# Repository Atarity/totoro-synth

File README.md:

# Totoro synth
Totoro is a portable, analog synth made on top of MCP6004 opamp. It features 2 VCOs (one could act as LFO) and simple VCF. Here it is [a short video demo](https://www.youtube.com/watch?v=yHeWAp9w_LM).

This open-source project based on [original design](https://syntherjack.net/totoro-1-ic-simple-synth/) of SyntherJack's Totoro and published with his permission.

In v1.0.1:
- Some of the components were rearranged
- Batteries moved on top side of PCB so overall assembly is almost 2 times thinner now
- Minor layout issues were fixed.

### Useful links
- [Bill of Materials v1.0.1](https://docs.google.com/spreadsheets/d/1fobkR_ruTiGQf1n50Jt4_U9o5RTrw8VCa_eaik46wdc/edit?usp=sharing)
- [Assembly details (RU)](https://snnkv.com/projects/totoro-slim/)
- [My list of open-source, standalone synths](https://diy-synths.snnkv.com/)

Enjoy the drone (under [CC-BY-NC-SA](https://creativecommons.org/licenses/by-nc-sa/4.0/deed.en))!

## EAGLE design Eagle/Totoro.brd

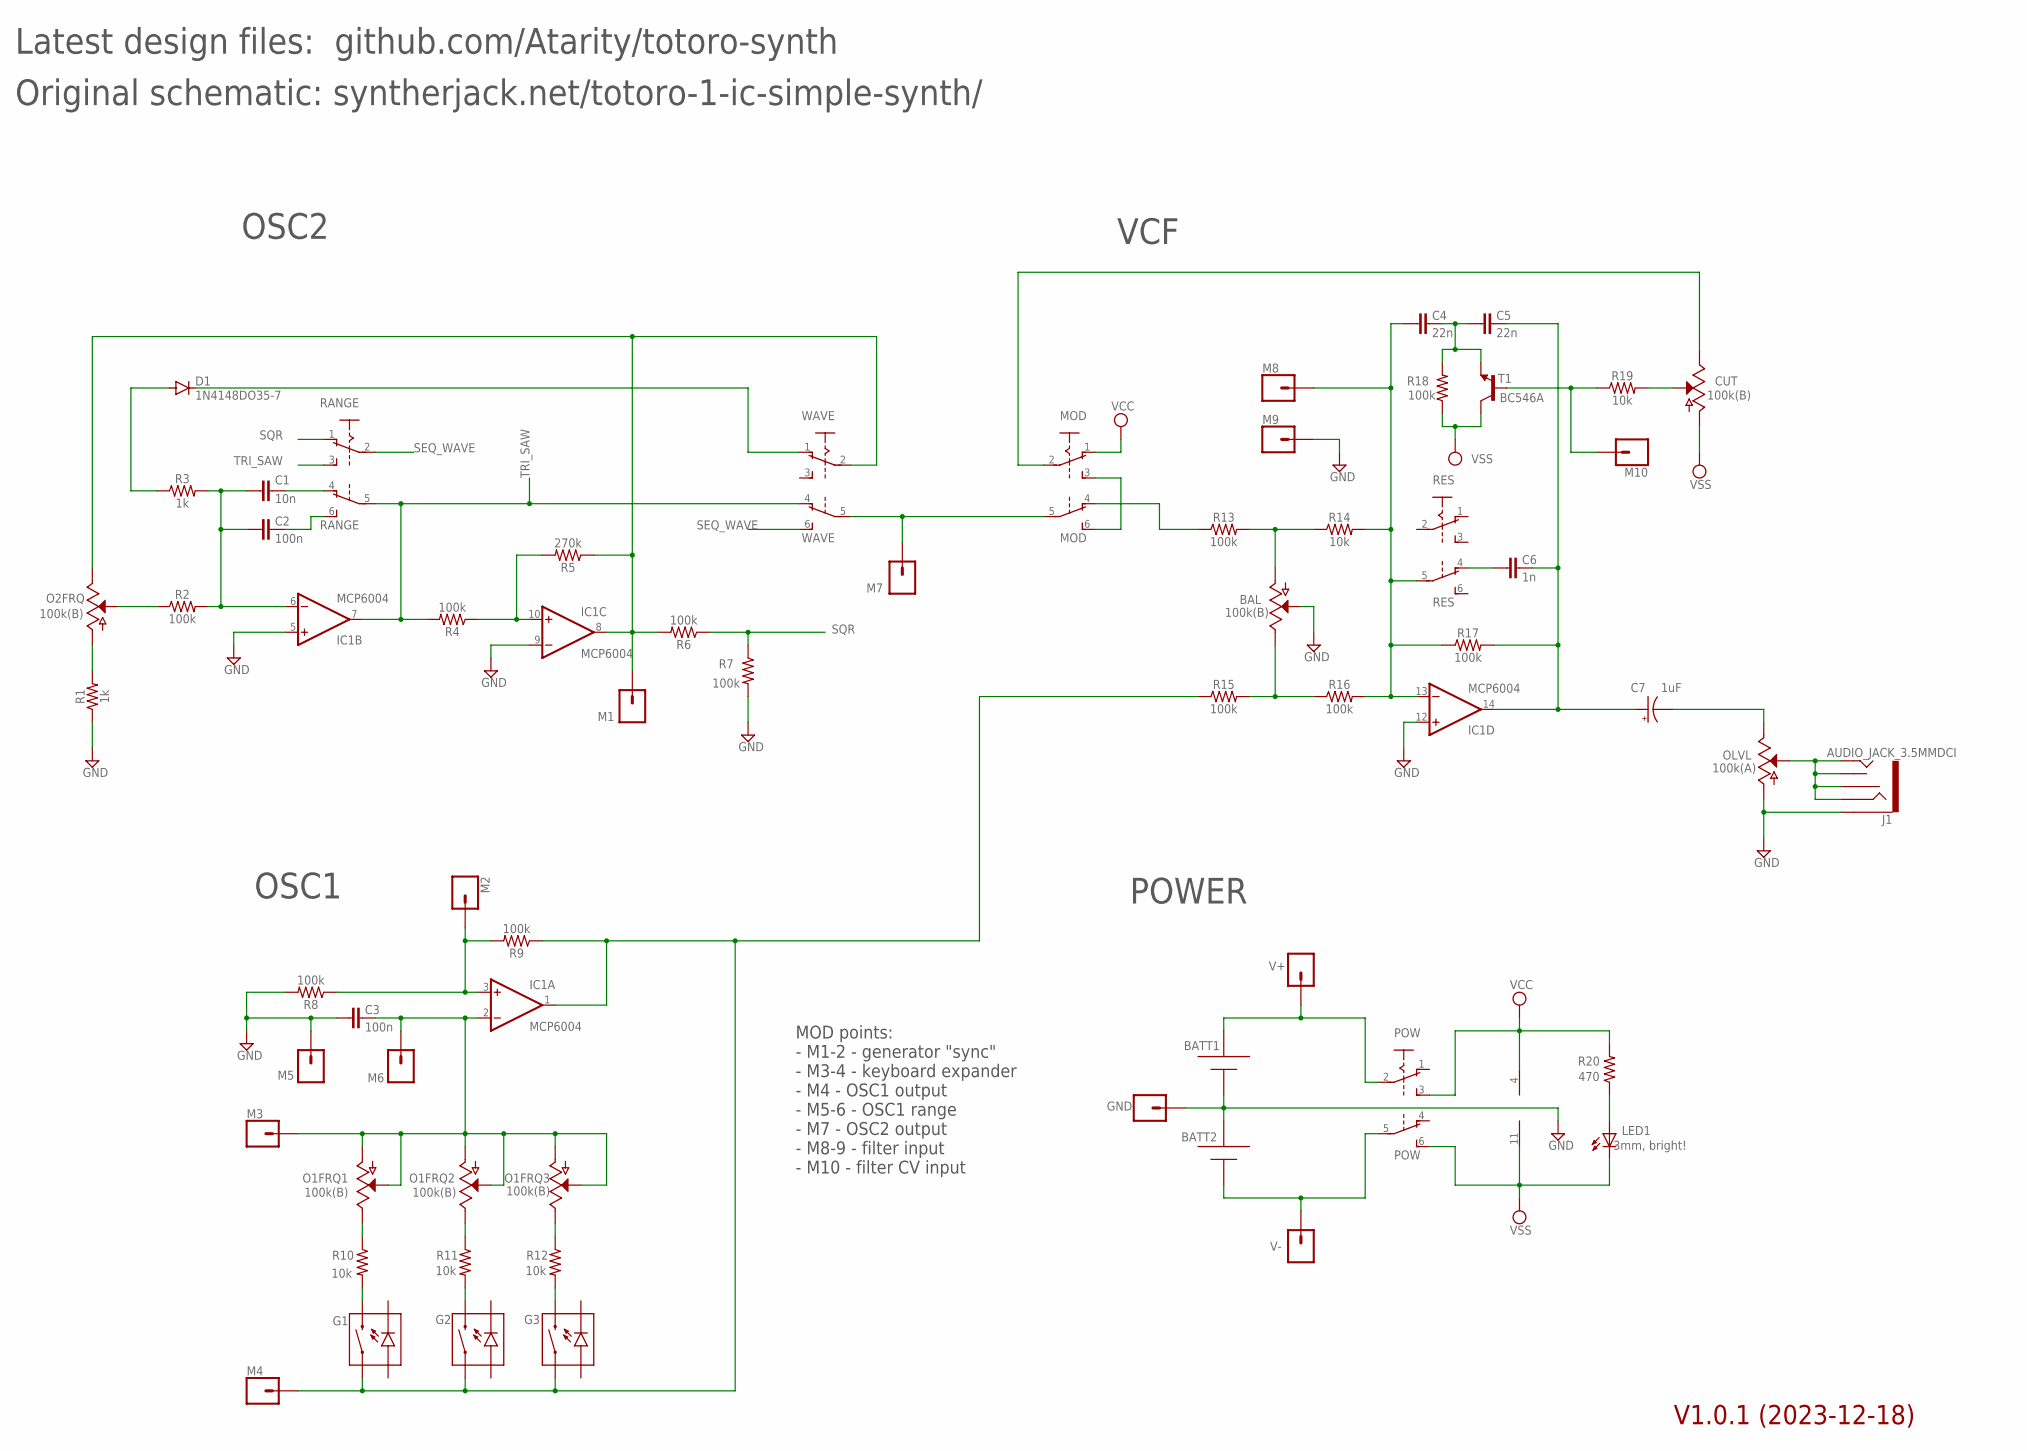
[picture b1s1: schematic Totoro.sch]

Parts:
BAL: 100k(B); POT-PTH-ALPS-KIT
BATT1, BATT2: ATARITY-AAAKLS5-817D; KLS5-817-D
C1: 10n; C050-024X044
C2, C3: 100n; C050-024X044
C4, C5: 22n; C050-024X044
C6: 1n; C050-024X044
C7: 1uF; CPOL-RADIAL-2.5MM-5MM
CUT: 100k(B); POT-PTH-ALPS-KIT
D1: 1N4148DO35-7; DO35-7
G1, G2, G3: MECHANICAL-KEYBOARD1U; CHERRY-MX-LED-1U
GND: CONN_01; 1X01
IC1: MCP6004; DIL14
J1: AUDIO_JACK_3.5MMDCI; DCI-ST-033
LED1: 3mm, bright!; LED3MM
M1, M2, M3, M4, M5, M6, M7, M8, M9, M10: CONN_01; 1X01
MOD: PB22E07
O1FRQ1, O1FRQ2, O1FRQ3, O2FRQ: 100k(B); POT-PTH-ALPS-KIT
OLVL: 100k(A); POT-PTH-ALPS-KIT
POW: PB22E07
R1, R3: 1k; AXIAL-0.3
R2, R4, R6, R7, R8, R9, R13, R15, R16, R17, R18: 100k; AXIAL-0.3
R5: 270k; AXIAL-0.3
R10, R11, R12, R14, R19: 10k; AXIAL-0.3
R20: 470; AXIAL-0.3
RANGE: PB22E07
RES: PB22E07
T1: BC546A; TO92-EBC
V+: CONN_01; 1X01
V-: CONN_01; 1X01
WAVE: PB22E07

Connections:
GND: BAL.P$2 (S), BATT1.+, BATT2.-, C3.2, GND.1, IC1.5 (+IN), IC1.9 (-IN), IC1.12 (+IN), J1.P2 (SLEEVE), J1.P3 (SLEEVE), M5.1, M9.1, OLVL.P$1 (A), R1.P$1 (1), R7.P$2 (2), R8.P$2 (2)
unnamed: C1.2, C2.2, IC1.6 (-IN), R2.P$2 (2), R3.P$2 (2)
unnamed: O2FRQ.P$2 (S), R2.P$1 (1)
unnamed: O2FRQ.P$1 (A), R1.P$2 (2)
unnamed: C1.1, RANGE.4 (O)
unnamed: C2.1, RANGE.6 (S)
unnamed: M7.1, MOD.5, WAVE.5
unnamed: IC1.10 (+IN), R4.P$1 (1), R5.P$2 (2)
unnamed: IC1.8 (OUT), M1.1, O2FRQ.P$3 (E), R5.P$1 (1), R6.P$2 (2), WAVE.2
unnamed: D1.A, R3.P$1 (1)
unnamed: D1.C, WAVE.1 (O)
unnamed: MOD.3 (S), MOD.6 (S)
unnamed: MOD.4 (O), R13.P$1 (1)
unnamed: BAL.P$3 (E), R15.P$2 (2), R16.P$1 (1)
unnamed: BAL.P$1 (A), R13.P$2 (2), R14.P$1 (1)
unnamed: C4.2, IC1.13 (-IN), M8.1, R14.P$2 (2), R16.P$2 (2), R17.P$1 (1), RES.5
unnamed: C6.2, RES.4 (O)
unnamed: C5.1, C6.1, C7.1 (+), IC1.14 (OUT), R17.P$2 (2)
unnamed: M10.1, R19.P$1 (1), T1.B
unnamed: C4.1, C5.2, R18.P$2 (2), T1.E
unnamed: CUT.P$2 (S), R19.P$2 (2)
unnamed: CUT.P$3 (E), MOD.2
unnamed: C7.2 (-), OLVL.P$3 (E)
unnamed: J1.P0 (TIP), J1.P1 (RING), J1.P4 (RSH), J1.P5 (TSH), OLVL.P$2 (S)
unnamed: O1FRQ3.P$3 (E), R12.P$1 (1)
unnamed: G1.S2 (2), R10.P$2 (2)
unnamed: O1FRQ2.P$3 (E), R11.P$1 (1)
unnamed: G2.S2 (2), R11.P$2 (2)
unnamed: O1FRQ1.P$3 (E), R10.P$1 (1)
unnamed: G3.S2 (2), R12.P$2 (2)
unnamed: C3.1, IC1.2 (-IN), M3.1, M6.1, O1FRQ1.P$1 (A), O1FRQ1.P$2 (S), O1FRQ2.P$1 (A), O1FRQ2.P$2 (S), O1FRQ3.P$1 (A), O1FRQ3.P$2 (S)
unnamed: IC1.3 (+IN), M2.1, R8.P$1 (1), R9.P$2 (2)
unnamed: G1.S1 (1), G2.S1 (1), G3.S1 (1), IC1.1 (OUT), M4.1, R9.P$1 (1), R15.P$1 (1)
unnamed: LED1.A, R20.P$1 (1)
unnamed: BATT1.-, POW.2, V+.1
unnamed: BATT2.+, POW.5, V-.1
SEQ_WAVE: RANGE.2, WAVE.6 (S)
SQR: R6.P$1 (1), R7.P$1 (1), RANGE.1 (O)
TRI_SAW: IC1.7 (OUT), R4.P$2 (2), RANGE.3 (S), RANGE.5, WAVE.4 (O)
VCC: IC1.4 (V+), MOD.1 (O), POW.3 (S), R20.P$2 (2)
VSS: CUT.P$1 (A), IC1.11 (V-), LED1.K (C), POW.6 (S), R18.P$1 (1), T1.C

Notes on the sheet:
Original schematic: syntherjack.net/totoro-1-ic-simple-synth/
OSC2
VCF
OSC1
POWER
Latest design files: github.com/Atarity/totoro-synth
V1.0.1 (2023-12-18)
MOD points: - M1-2 - generator "sync" - M3-4 - keyboard expander - M4 - OSC1 output - M5-6 - OSC1 range - M7 - OSC2 output - M8-9 - filter input - M10 - filter CV input

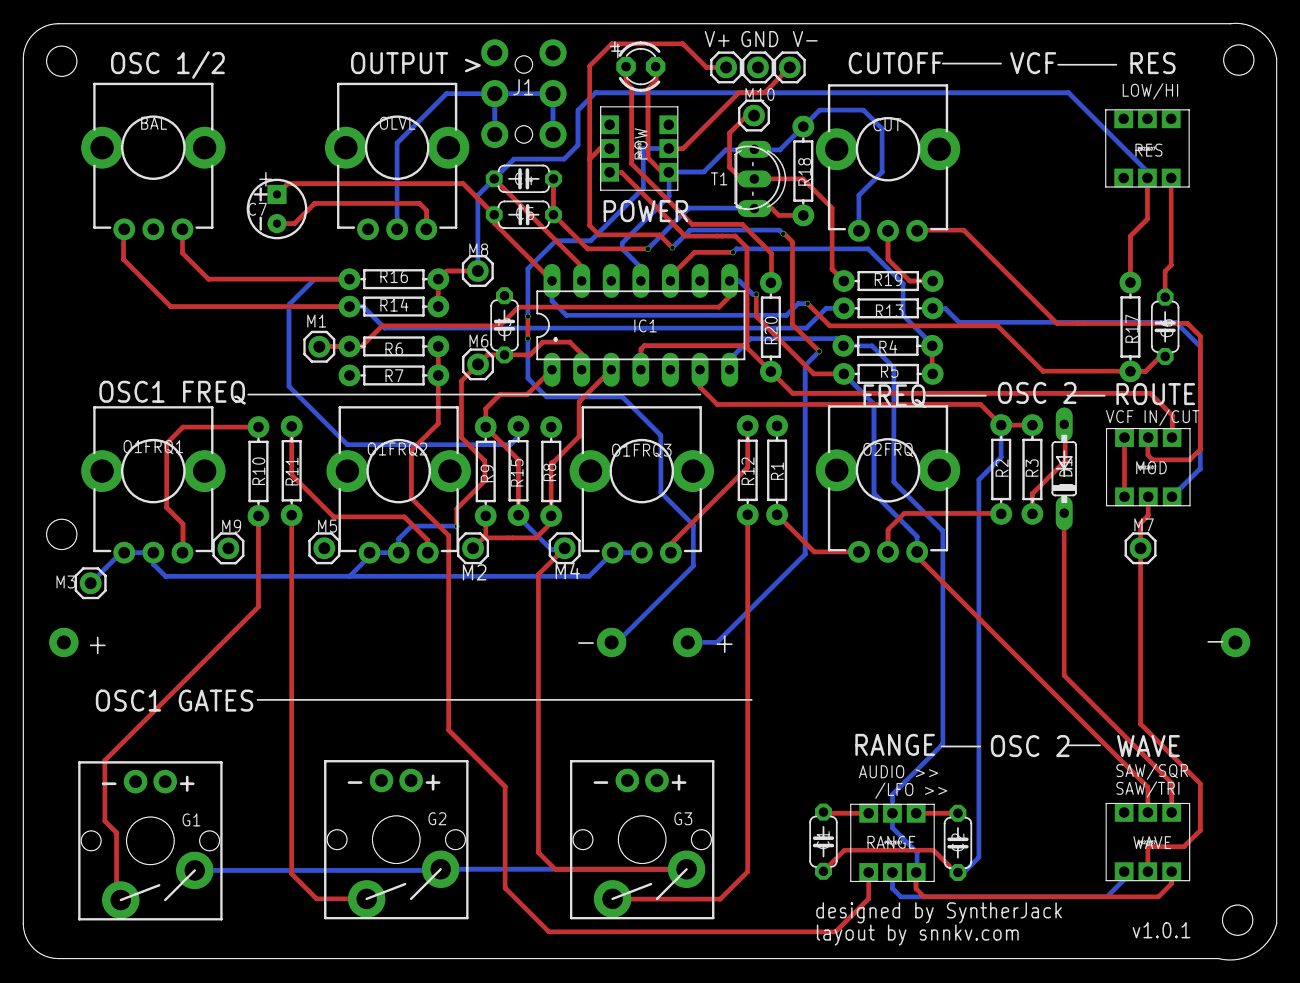
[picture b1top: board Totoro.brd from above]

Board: 2 copper layers, 107.5 x 80.4 mm, 62 parts (0 on the bottom side), 41 nets.

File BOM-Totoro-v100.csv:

Qty,Designator,Value,Package,Device,Chip-i-Dip,Ali,LCSC
2,"R1, R3",1k,"AXIAL-0.3, 0.25W","Thru-hole resistor 0.25W, 5%",,,
11,"R2, R4, R6, R7, R8, R9, R13, R15, R16, R17, R18",100k,"AXIAL-0.3, 0.25W","Thru-hole resistor 0.25W, 5%",,,
1,R5,270k,"AXIAL-0.3, 0.25W","Thru-hole resistor 0.25W, 5%",,,
5,"R10, R11, R12, R14, R19",10k,"AXIAL-0.3, 0.25W","Thru-hole resistor 0.25W, 5%",,,
1,R20,470,"AXIAL-0.3, 0.25W","Thru-hole resistor 0.25W, 5%",,,
6,"BAL, CUT, O1FRQ, O1FRQ1, O1FRQ2, O1FRQ3",10k(B),"9mm, best with 25mm overall height and star shaft",RV09 pot with B char,,RK09,C3020616 ???
1,OLVL,10k(A),"9mm, best with 25mm overall height and star shaft",RV09 pot with A char,,,
1,C1,10n,C050-024X044,Ceramic,,,
2,"C2, C3",100n,C050-024X044,Ceramic,,,
2,"C4, C5",22n,C050-024X044,Ceramic,,,
1,C6,1n,C050-024X044,Film or ceramic,,,C401093
1,C7,1uF,CPOL-RADIAL-2.5MM-5MM,"10UF-POLAR-RADIAL-2.5MM-25V-20% Electrolithic, polarized cap, height less than 10mm",,,
1,D1,1N4148,DO35-7,Diode,1N4148,,C493188
1,LED1,"3mm, bright!",LED3MM,,L-7104LGD,,C125082
5,"MOD, POW, RANGE, RES, WAVE",,PB22E07,Push switch with latching PB22E07,PS700L,PB22E07,C2911140
2,"BATT1, BATT2",AAA,KLS5-817-D,AAA battery holder,KLS5-817-D,,C5290189
1,J1,AUDIO_JACK_3.5,DCI-ST-033,AUDIO_JACK_3.5MMDCI,,,C179783
1,T1,BC546A,TO-92-AMMO,TRANSISTOR_PNPBC558,BC546A,,C896668
1,IC1,MCP6004,DIL14,Operational Amplifier,MCP6004-EP,,C645761
3,"G1, G2, G3",RED,CHERRY-MX-LED-1U,Cherry MX 1U KB switch,,MX red,
,,,,,,,
,,,,,,,
1,,,DIL14,DIP IC test bed,SCS-14,,C132508
5,,,,Caps for push switches,,,
7,,,,Knobs,,,

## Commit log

2022-02-23 hw-v010
2022-05-06 pic, outdated gerbers
2022-05-06 ds_store cache clear
2022-05-06 cache fix
2023-08-08 v100 added with minor fixes and ontop batteries
2023-12-16 version 101
2023-12-16 license ref added
2023-12-17 video link added
2023-12-18 100k pot fix
2023-12-18 readme typo
2023-12-28 project url updated
2025-03-29 Transistor symbol fix

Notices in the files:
parts and their libraries:
SparkFun-Resistors: Licensing: Creative Commons ShareAlike 4.0 International - https://creativecommons.org/licenses/by-sa/4.0
